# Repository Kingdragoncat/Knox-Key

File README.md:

# Knox Key

This is a custom USB-C FIDO2 security key. The repository contains the KiCad 9 hardware files (schematics, PCB layout, fab outputs) and the authenticator firmware. 

The hardware pairs an STM32L433 microcontroller with an ATECC608B secure element. The project started out as an STM32F072 design (originally named "kryptonite") but was later reworked to use the L433.

## Hardware Details
* **MCU:** STM32L433CB (LQFP-48) with an 8 MHz crystal and internal USB PHY.
* **Crypto:** ATECC608B secure element on I2C (PB6/PB7) for hardware TRNG.
* **Port:** USB Type-C running USB 2.0 full speed.
* **Feedback:** Single RGB LED. Green is success, red is error, blue/yellow indicates waiting for user presence.
* **Button:** Tactile button for user presence verification (supports single, double, and long presses).
* **Power:** USB bus-powered via a 3.3V MCP1700 LDO.
* **PCB:** 2-layer layout.

## Working with KiCad
Open `Knox Key Kicad.kicad_pro` in KiCad 9. Make sure to run ERC and DRC before exporting manufacturing outputs. If you are hand-assembling the board, open `bom/ibom.html` in a web browser for the interactive BOM.

## Firmware
The firmware is in `firmware/knoxkey/` and implements a FIDO2 / CTAP2 authenticator. Random numbers are pulled from the ATECC608B over I2C, while credential wrapping uses software AES. User presence is verified via the hardware button.

To build the target for the STM32L433:
```bash
cd firmware/knoxkey
cmake -B build/stm32l433-release -S . --preset default -DBUILD_TARGET=stm32l433
cmake --build build/stm32l433-release -j 8
```
Binaries (`.elf`, `.hex`, `.bin`) will compile into `build/stm32l433-release/targets/stm32l433/`. Flash them using an ST-Link or via USB DFU mode.

## Bill of Materials
17 line items, 29 components total. Machine-readable versions: [`BOM.csv`](BOM.csv) and [`BOM.md`](BOM.md). `manufacturing/bom.csv` has the same data in the exact format JLCPCB's assembly service expects.

| Designator | Qty | Value | Footprint | Description | LCSC Part # |
|---|---|---|---|---|---|
| C1, C11, C12 | 3 | 10u | 0603 | Bulk/decoupling capacitor | [C466781](https://www.lcsc.com/product-detail/C466781.html) |
| C10, C2, C3, C4, C5, C6, C7 | 7 | 100n | 0402 | Decoupling capacitor | [C6119799](https://www.lcsc.com/product-detail/C6119799.html) |
| C8, C9 | 2 | 33p | 0402 | Crystal load capacitor | [C696910](https://www.lcsc.com/product-detail/C696910.html) |
| D1 | 1 | ASMB-MTB1-0A3A2 | LED_Avago_PLCC4_3.2x2.8mm_CW | RGB status LED | — |
| J3 | 1 | Conn_01x05 | PinHeader_1x05_P2.54mm_Vertical | SWD debug header | — |
| P1 | 1 | USB_C_Plug_USB2.0 | TYPE-C-31-G-01 | USB Type-C receptacle | [C530605](https://www.lcsc.com/product-detail/C530605.html) |
| R1, R5 | 2 | 10k | 0402 | Pull-up resistor | [C60490](https://www.lcsc.com/product-detail/C60490.html) |
| R2, R3, R4 | 3 | 4k7 | 0402 | USB CC pull-down / series resistor | [C25940](https://www.lcsc.com/product-detail/C25940.html) |
| R6 | 1 | R* | 0402 | RGB LED red channel current-limiting resistor | — |
| R7 | 1 | G* | 0402 | RGB LED green channel current-limiting resistor | — |
| R8 | 1 | B* | 0402 | RGB LED blue channel current-limiting resistor | — |
| SW1 | 1 | SW_Push | SW_Push_1P1T_XKB_TS-1187A | User presence tactile button | [C318884](https://www.lcsc.com/product-detail/C318884.html) |
| U2 | 1 | ATECC608B-MAHDA | DFN-8-1EP_3x2mm_P0.5mm_EP1.3x1.5mm | Cryptographic secure element | [C1518773](https://www.lcsc.com/product-detail/C1518773.html) |
| U3 | 1 | MCP1700x-330xxTT | SOT-23 | 3.3V LDO regulator | [C39051](https://www.lcsc.com/product-detail/C39051.html) |
| U4 | 1 | USBLC6-2SC6 | SOT-23-6 | USB D+/D- ESD protection | [C7519](https://www.lcsc.com/product-detail/C7519.html) |
| U6 | 1 | STM32L433CBTx | LQFP-48_7x7mm_P0.5mm | Main microcontroller | — |
| Y1 | 1 | 8MHz | Crystal_SMD_3225-4Pin_3.2x2.5mm | Crystal oscillator | [C720915](https://www.lcsc.com/product-detail/C720915.html) |

\* R6/R7/R8 are still labeled with placeholder values (`R`/`G`/`B`) in the schematic rather than an actual resistance — confirm before ordering a board that needs them populated.

## Manufacturing & Ordering
All files needed to manufacture the board are inside `manufacturing/`:
* `gerbers/` and `knox-key-gerbers.zip` — Bare-board fabrication files.
* `bom.csv` — Bill of Materials (with LCSC part numbers).
* `positions.csv` — Pick-and-place component coordinates (CPL).
* `designators.csv` — Reference designator mappings.
* `netlist.ipc` — IPC-D-356 netlist.

For JLCPCB: Upload `knox-key-gerbers.zip` for the PCB, and use `bom.csv` and `positions.csv` for SMT assembly. Add a solder paste stencil to your order if you plan to solder manually. Don't forget to regenerate these from KiCad if you modify the layout!

## Renders

## Security Warning
This is a hobbyist project and has not undergone any formal security audit. The ATECC608B chips ship unprovisioned, meaning you must load your own keys onto the secure element. Do not use this for production environments without reviewing the firmware and provisioning process yourself.

## License
GPLv3. See `LICENSE` for details.

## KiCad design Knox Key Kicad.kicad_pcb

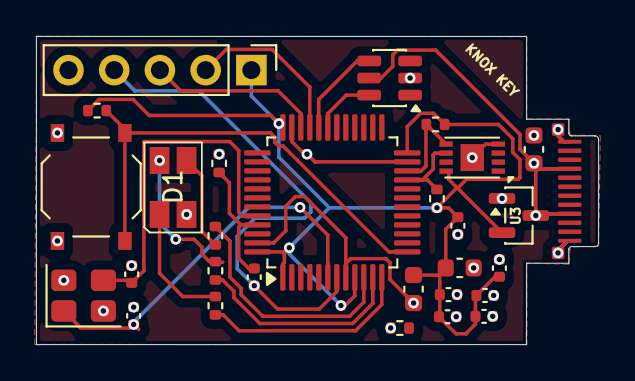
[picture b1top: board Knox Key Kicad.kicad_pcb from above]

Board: 2 copper layers, 31.2 x 17.1 mm, 29 parts (0 on the bottom side), 20 nets.

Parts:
C1, C11, C12: 10u; C_0603_1608Metric
C2, C3, C4, C5, C6, C7, C10: 100n; C_0402_1005Metric
C8, C9: 33p; C_0402_1005Metric
D1: ASMB-MTB1-0A3A2; LED_Avago_PLCC4_3.2x2.8mm_CW
J3: Conn_01x05; PinHeader_1x05_P2.54mm_Vertical
P1: USB_C_Plug_USB2.0; TYPE-C-31-G-01
R1, R5: 10k; R_0402_1005Metric
R2, R3, R4: 4k7; R_0402_1005Metric
R6: R; R_0402_1005Metric
R7: G; R_0402_1005Metric
R8: B; R_0402_1005Metric
SW1: SW_Push; SW_Push_1P1T_XKB_TS-1187A
U2: ATECC608B-MAHDA; DFN-8-1EP_3x2mm_P0.5mm_EP1.3x1.5mm
U3: MCP1700x-330xxTT; SOT-23
U4: USBLC6-2SC6; SOT-23-6
U6: STM32L433CBTx; LQFP-48_7x7mm_P0.5mm
Y1: 8MHz; Crystal_SMD_3225-4Pin_3.2x2.5mm

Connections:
+3V3: C1.1, C2.1, C3.1, C4.1, C5.1, C6.1, C10.1, C12.1, J3.1, R2.1, R3.1, R5.2, U2.8 (VCC), U3.2 (VO), U6.1 (VBAT), U6.9 (VDDA), U6.24 (VDD), U6.36 (VDD), U6.48 (VDD)
/BOOT0: C7.1, R1.2, U6.45 (PB8)
/BTN: R5.1, SW1.1, U6.13 (PA3)
/HSE_IN: C8.1, U6.6 (PH1), Y1.1
/HSE_OUT: C9.1, U6.44 (PH3), Y1.3
/LED_RGBK_B: R8.2, U6.12 (PA2)
/LED_RGBK_G: R7.2, U6.11 (PA1)
/LED_RGBK_R: R6.2, U6.10 (PA0)
/NRST: C7.2, J3.4, U6.7 (NRST)
/SCL: R3.2, U2.6 (SCL), U6.21 (PB10)
/SDA: R2.2, U2.5 (SDA), U6.22 (PB11)
/SWCLK: J3.3, U6.34 (PA13)
/SWDIO: J3.2, U6.33 (PA12)
GND: C1.2, C2.2, C3.2, C4.2, C5.2, C6.2, C8.2, C9.2, C10.2, C11.2, C12.2, D1.4 (A), J3.5, P1.A1 (GND), P1.A12 (GND), P1.B1 (GND), P1.B12 (GND), R1.1, R4.1, SW1.2, U2.4 (GND), U2.9 (EP), U3.1 (GND), U4.2 (GND), U6.8 (VSSA), U6.23 (VSS), U6.35 (VSS), U6.47 (VSS), Y1.2, Y1.4
unnamed: D1.3 (BK), R6.1
unnamed: D1.2 (GK), R7.1
unnamed: D1.1 (RK), R8.1
USB_D+: U4.4 (I/O2), U6.32 (PA11)
USB_D-: U4.6 (I/O1), U6.31 (PA10)
VBUS: C11.1, P1.A4 (VBUS), P1.A9 (VBUS), P1.B4 (VBUS), P1.B9 (VBUS), U3.3 (VI), U4.5 (VBUS)

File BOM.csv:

Designator,Quantity,Value,Footprint,Description,LCSC Part #
"C1, C11, C12",3,10u,0603,Bulk/decoupling capacitor,C466781
"C10, C2, C3, C4, C5, C6, C7",7,100n,0402,Decoupling capacitor,C6119799
"C8, C9",2,33p,0402,Crystal load capacitor,C696910
D1,1,ASMB-MTB1-0A3A2,LED_Avago_PLCC4_3.2x2.8mm_CW,RGB status LED,
J3,1,Conn_01x05,PinHeader_1x05_P2.54mm_Vertical,SWD debug header,
P1,1,USB_C_Plug_USB2.0,TYPE-C-31-G-01,USB Type-C receptacle,C530605
"R1, R5",2,10k,0402,Pull-up resistor,C60490
"R2, R3, R4",3,4k7,0402,USB CC pull-down / series resistor,C25940
R6,1,R*,0402,RGB LED red channel current-limiting resistor,
R7,1,G*,0402,RGB LED green channel current-limiting resistor,
R8,1,B*,0402,RGB LED blue channel current-limiting resistor,
SW1,1,SW_Push,SW_Push_1P1T_XKB_TS-1187A,User presence tactile button,C318884
U2,1,ATECC608B-MAHDA,DFN-8-1EP_3x2mm_P0.5mm_EP1.3x1.5mm,Cryptographic secure element,C1518773
U3,1,MCP1700x-330xxTT,SOT-23,3.3V LDO regulator,C39051
U4,1,USBLC6-2SC6,SOT-23-6,USB D+/D- ESD protection,C7519
U6,1,STM32L433CBTx,LQFP-48_7x7mm_P0.5mm,Main microcontroller,
Y1,1,8MHz,Crystal_SMD_3225-4Pin_3.2x2.5mm,Crystal oscillator,C720915

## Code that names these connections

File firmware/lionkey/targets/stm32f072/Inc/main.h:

/**
 ******************************************************************************
 * @file           : main.h
 * @brief          : Header for main.c file.
 *                   Knox Key STM32F072 target.
 ******************************************************************************
 */

#ifndef __MAIN_H
#define __MAIN_H

#ifdef __cplusplus
extern "C" {
#endif

/* Includes ------------------------------------------------------------------*/
#include "stm32f0xx_hal.h"
#include <stdio.h>

/* Exported types ------------------------------------------------------------*/

extern __IO uint32_t ButtonState;

#define BUTTON_RELEASED  0
#define BUTTON_PRESSED   1

/* Exported functions prototypes ---------------------------------------------*/
void Error_Handler(void);

int Debug_UART_Get_Byte(void);

typedef enum Status_LED_Mode {
	STATUS_LED_MODE_OFF = 0,
	STATUS_LED_MODE_ON = 1,
	STATUS_LED_MODE_BLINKING_NORMAL = 2,
	STATUS_LED_MODE_BLINKING_SPECIAL = 3,
} Status_LED_Mode;

void Status_LED_Set_Mode(Status_LED_Mode mode);

void HAL_TIM_MspPostInit(TIM_HandleTypeDef *htim);

/* Private defines -----------------------------------------------------------*/
/* Knox Key board pin assignments (from schematic) */

/* Status LED - PA0 (active high, optional replace with RGB) */
#define STATUS_LED_Pin        GPIO_PIN_0
#define STATUS_LED_GPIO_Port  GPIOA

/* User button - PA1 */
#define USER_BTN_Pin          GPIO_PIN_1
#define USER_BTN_GPIO_Port    GPIOA

/* ATECC608B I2C - PB6 (SCL), PB7 (SDA) */
#define ATECC_SCL_Pin         GPIO_PIN_6
#define ATECC_SCL_GPIO_Port   GPIOB
#define ATECC_SDA_Pin         GPIO_PIN_7
#define ATECC_SDA_GPIO_Port   GPIOB

/* USB D+ / D- are on PA11 / PA12 (handled by USB peripheral) */

/* SWD debug - PA13 (SWDIO), PA14 (SWCLK) */
#define SWDIO_Pin             GPIO_PIN_13
#define SWDIO_GPIO_Port       GPIOA
#define SWCLK_Pin             GPIO_PIN_14
#define SWCLK_GPIO_Port       GPIOA

#ifdef __cplusplus
}
#endif

#endif /* __MAIN_H */

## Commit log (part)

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2026-05-02 Initial commit of Knox Key hardware files
2026-05-02 refactor: clean repository and remove kryptonite references
    - Organize directories: manufacturing-kryptonite/ → manufacturing/, img-kryptonite/ → design-images/
    - Rename backup directories: backup-kryptonite-* → backup-*
    - Rename DESIGN updates: README-kryptonite-update.md → DESIGN-UPDATES.md
    - Update all gerber files and manufacturing outputs: kryptonite-* → knox-key-*
    - Rename position file: kryptonite-pos.csv → component-positions.csv
    - Add comprehensive .gitignore for KiCad projects
2026-05-02 docs: remove design-updates doc and add GPLv3 license
    - Remove DESIGN-UPDATES.md and references
    - Add GPLv3 LICENSE file
    - Simplify README MCU and verification notes
    - Update contributing and organization summary
2026-05-08 Ignore KiCad backups and caches
2026-05-08 Reorganize hardware layout
2026-05-11 Update README: Embed new design renders, update to STM32L433, add ATECC608B FIDO details, and remove emojis
2026-05-11 Add full firmware port to repository
2026-05-11 Add Firmware & FIDO2 Support section to README
2026-05-11 Rename firmware from lionkey to knoxkey globally and add specific firmware README
2026-05-11 Update project structure tree in README to include firmware directory
2026-05-11 Remove empty README from firmware folder
2026-05-28 docs: add project journal, map screenshots, and update firmware code/configs
2026-05-28 chore: ignore freerouting temporary files, production artifacts, and local config
2026-05-28 feat: add JLCPCB production BOM, placement, and fab archive
2026-05-28 Remove project overview from JOURNAL.md
    Removed project overview section from JOURNAL.md
2026-05-28 Update project journal title and formatting
2026-05-28 Update JOURNAL.md
    Remove start date from the project journal.
2026-05-28 Update JOURNAL.md to remove project note
    Removed project note from the journal entry.
2026-05-29 docs: format JOURNAL.md as a daily devlog with frontmatter and screenshot mappings
2026-05-30 docs: add missing design and 3D render images referenced in README.md
2026-06-04 refactor: combine production and manufacturing directories into manufacturing/
2026-06-04 docs: simplify README with a natural developer-focused tone
